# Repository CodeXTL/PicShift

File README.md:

# PicShift
## Overview
Welcome to the overview of the project (currently) known as PixShift. Inspired by the DIY Image Sensor and Digital Camera by Sean Hodgins (source), the goal of this project is to create a portable camera with a 64-pixel camera sensor that is mounted on a mechanically shifted stage so that images at a higher resolution can be obtained. The camera sensor will be created from scratch by laying out an 8 by 8 grid of light sensors (or phototransistors) on a custom PCB. Since an 8 pixels by 8 pixels image is not very interesting, we will mount the camera sensor PCB on a motorized mechanical XY stage so that we may shift the small senser over a wider area to capture multiple samples in order to stitch them into a higher resolution image. The stitching of samples will be done through software on a STM32F411RET6 microcontroller, residing on the NUCLEO-F411RE development board. The resulting image data will be saved onto a microSD card through a breakout board. For focusing the light onto the sensible region, we plan on using an existing convex lense (perhaps a magnifying lens or some kind of camera lens) 

## Objectives
-	Design and create a working PCB for an array of 8 by 8 light sensors
-	Design and create a mechanical XY stage in a small form factor.
-	Design and create a body to house all components so that the final project is portable.

## Expectation
The expectation for the project is quite simple. The final product should be able to take an image at the click of a button, store that image onto a microSD card, and when we open the image on a computer, it should resemble the scene. If it can do all that, that is an ‘A’. And the measure of even greater success would just be how much more we can make the image resemble the scene; the clear, the better. 

## Mid-Project Review Goal
By the time of the mid-project review, I aim to have the following deliverables:
-	A working camera sensor PCB
-	A prototype for the motorized XY stage

## Cost
Work-in Progress

## Resources
-	Instructables: DIY Image Sensor and Digital Camera
  -	Github: LINK
-	YouTube: Microscope Automated XY Stage: 3D Printing test
  - They salvaged a CD-ROM drive and made a highly precise XY stage for microscope slides
  - The motor from the CD-ROM drive is apparently called a sled motor, which seems like a stepper motor attached to a very long screw (might look for alternatives if it becomes hard to acquire an old CD drive)
-	st.com: User Manual for NUCLEO-F411RE
-	DigiKey: ALS-PT19-315C/L177/TR8
-	LCSC: EVERLIGHT ALS-PT19-315C/L177/TR8

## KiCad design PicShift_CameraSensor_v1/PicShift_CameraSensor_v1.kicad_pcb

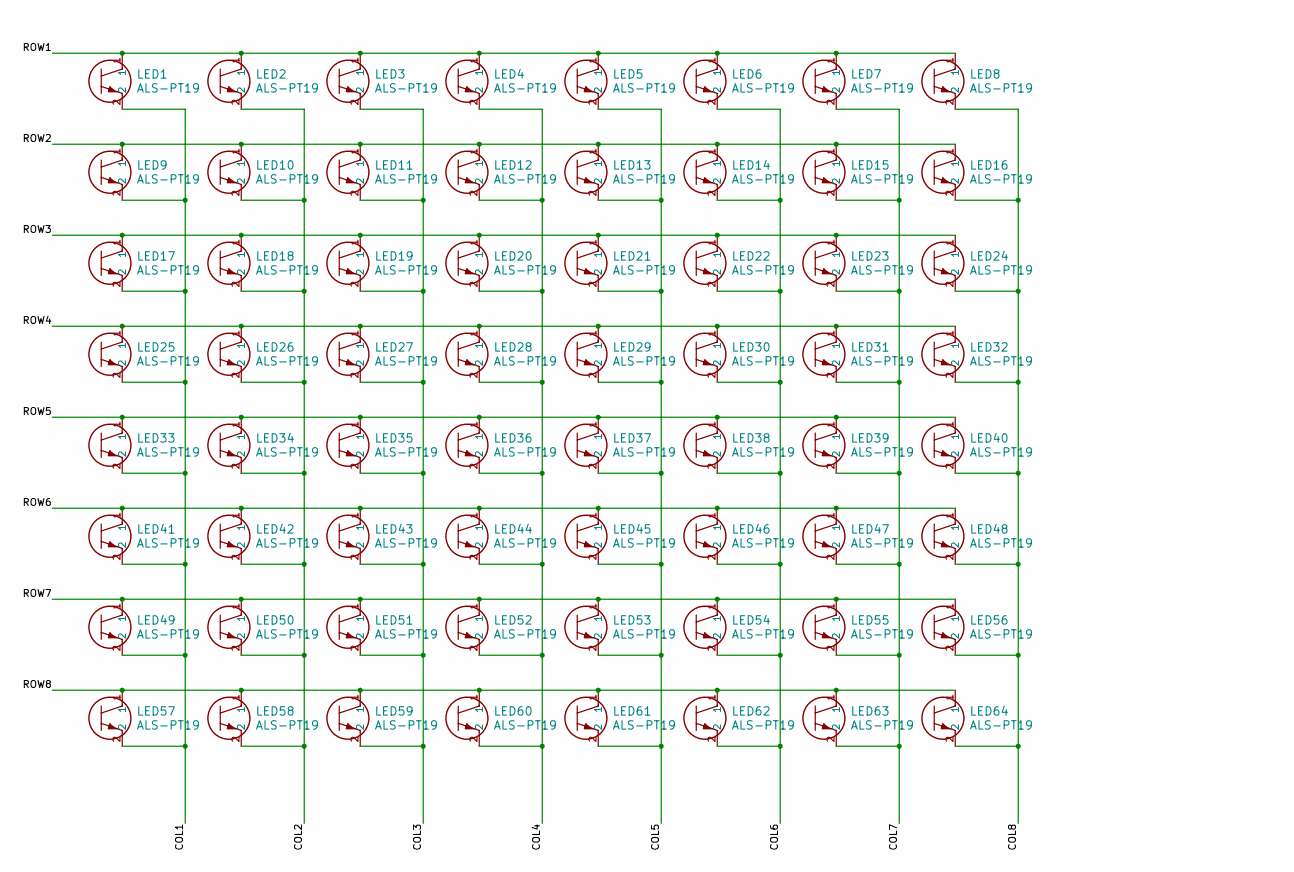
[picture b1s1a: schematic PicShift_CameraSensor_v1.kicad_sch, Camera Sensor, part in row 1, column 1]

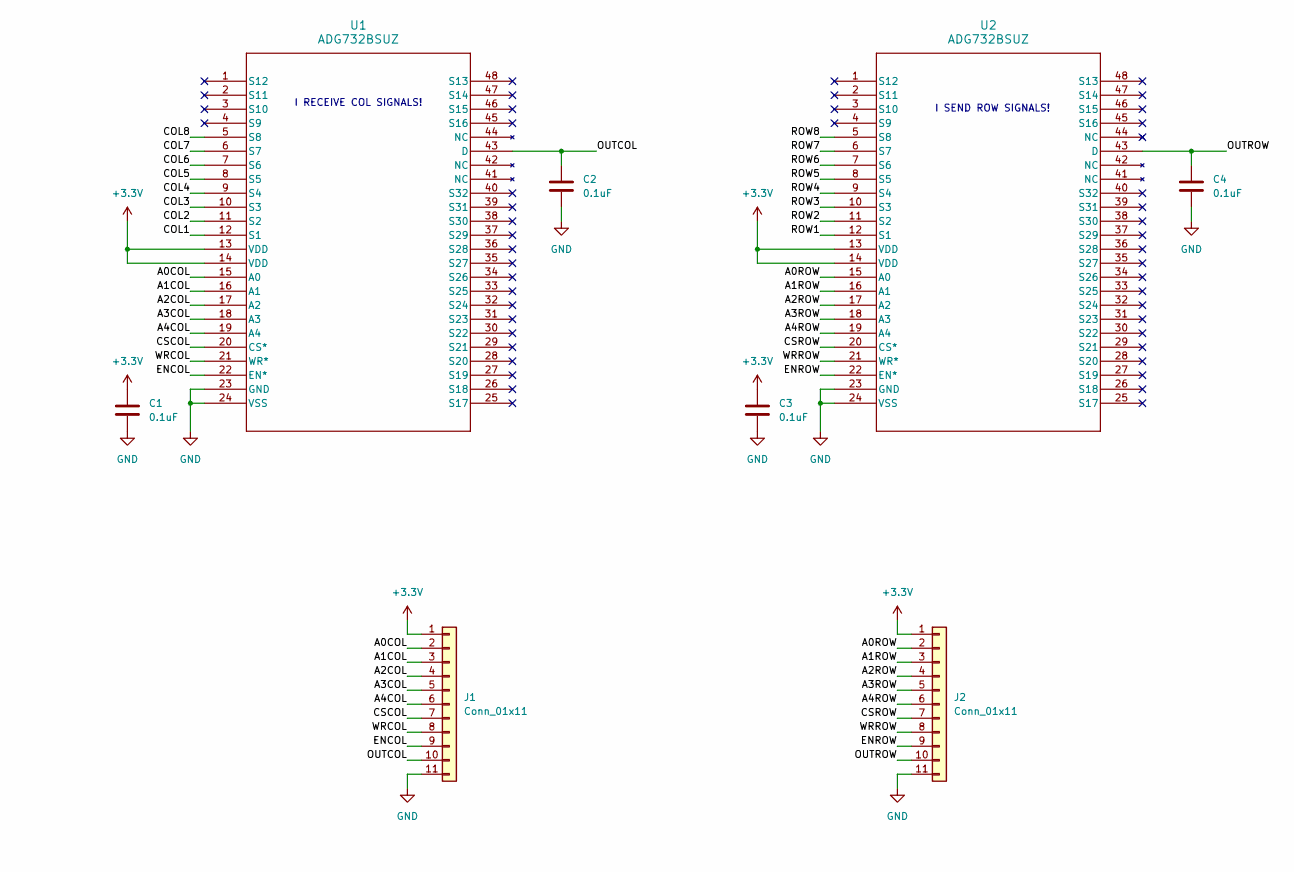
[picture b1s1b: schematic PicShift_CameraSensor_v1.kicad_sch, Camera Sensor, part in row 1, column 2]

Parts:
C1, C2, C3, C4: 0.1uF; C_0805_2012Metric_Pad1.18x1.45mm_HandSolder
J1, J2: Conn_01x11; PinHeader_1x11_P1.00mm_Vertical
LED1, LED2, LED3, LED4, LED5, LED6, LED7, LED8, LED9, LED10, LED11, LED12, LED13, LED14, LED15, LED16, LED17, LED18, LED19, LED20, LED21, LED22, LED23, LED24, LED25, LED26, LED27, LED28, LED29, LED30, LED31, LED32, LED33, LED34, LED35, LED36, LED37, LED38, LED39, LED40, LED41, LED42, LED43, LED44, LED45, LED46, LED47, LED48, LED49, LED50, LED51, LED52, LED53, LED54, LED55, LED56, LED57, LED58, LED59, LED60, LED61, LED62, LED63, LED64: ALS-PT19; LED_77&slash_TR8_EVE
U1, U2: ADG732BSUZ; SU_48_ADI

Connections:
+3.3V: C1.1, C3.1, J1.1, J2.1, U1.13 (VDD), U1.14 (VDD), U2.13 (VDD), U2.14 (VDD)
/A0COL: J1.2, U1.15 (A0)
/A0ROW: J2.2, U2.15 (A0)
/A1COL: J1.3, U1.16 (A1)
/A1ROW: J2.3, U2.16 (A1)
/A2COL: J1.4, U1.17 (A2)
/A2ROW: J2.4, U2.17 (A2)
/A3COL: J1.5, U1.18 (A3)
/A3ROW: J2.5, U2.18 (A3)
/A4COL: J1.6, U1.19 (A4)
/A4ROW: J2.6, U2.19 (A4)
/COL1: LED1.2, LED9.2, LED17.2, LED25.2, LED33.2, LED41.2, LED49.2, LED57.2, U1.12 (S1)
/COL2: LED2.2, LED10.2, LED18.2, LED26.2, LED34.2, LED42.2, LED50.2, LED58.2, U1.11 (S2)
/COL3: LED3.2, LED11.2, LED19.2, LED27.2, LED35.2, LED43.2, LED51.2, LED59.2, U1.10 (S3)
/COL4: LED4.2, LED12.2, LED20.2, LED28.2, LED36.2, LED44.2, LED52.2, LED60.2, U1.9 (S4)
/COL5: LED5.2, LED13.2, LED21.2, LED29.2, LED37.2, LED45.2, LED53.2, LED61.2, U1.8 (S5)
/COL6: LED6.2, LED14.2, LED22.2, LED30.2, LED38.2, LED46.2, LED54.2, LED62.2, U1.7 (S6)
/COL7: LED7.2, LED15.2, LED23.2, LED31.2, LED39.2, LED47.2, LED55.2, LED63.2, U1.6 (S7)
/COL8: LED8.2, LED16.2, LED24.2, LED32.2, LED40.2, LED48.2, LED56.2, LED64.2, U1.5 (S8)
/CSCOL: J1.7, U1.20 (CS*)
/CSROW: J2.7, U2.20 (CS*)
/ENCOL: J1.9, U1.22 (EN*)
/ENROW: J2.9, U2.22 (EN*)
/OUTCOL: C2.1, J1.10, U1.43 (D)
/OUTROW: C4.1, J2.10, U2.43 (D)
/ROW1: LED1.1, LED2.1, LED3.1, LED4.1, LED5.1, LED6.1, LED7.1, LED8.1, U2.12 (S1)
/ROW2: LED9.1, LED10.1, LED11.1, LED12.1, LED13.1, LED14.1, LED15.1, LED16.1, U2.11 (S2)
/ROW3: LED17.1, LED18.1, LED19.1, LED20.1, LED21.1, LED22.1, LED23.1, LED24.1, U2.10 (S3)
/ROW4: LED25.1, LED26.1, LED27.1, LED28.1, LED29.1, LED30.1, LED31.1, LED32.1, U2.9 (S4)
/ROW5: LED33.1, LED34.1, LED35.1, LED36.1, LED37.1, LED38.1, LED39.1, LED40.1, U2.8 (S5)
/ROW6: LED41.1, LED42.1, LED43.1, LED44.1, LED45.1, LED46.1, LED47.1, LED48.1, U2.7 (S6)
/ROW7: LED49.1, LED50.1, LED51.1, LED52.1, LED53.1, LED54.1, LED55.1, LED56.1, U2.6 (S7)
/ROW8: LED57.1, LED58.1, LED59.1, LED60.1, LED61.1, LED62.1, LED63.1, LED64.1, U2.5 (S8)
/WRCOL: J1.8, U1.21 (WR*)
/WRROW: J2.8, U2.21 (WR*)
GND: C1.2, C2.2, C3.2, C4.2, J1.11, J2.11, U1.23 (GND), U1.24 (VSS), U2.23 (GND), U2.24 (VSS)

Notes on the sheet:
I SEND ROW SIGNALS!
I RECEIVE COL SIGNALS!

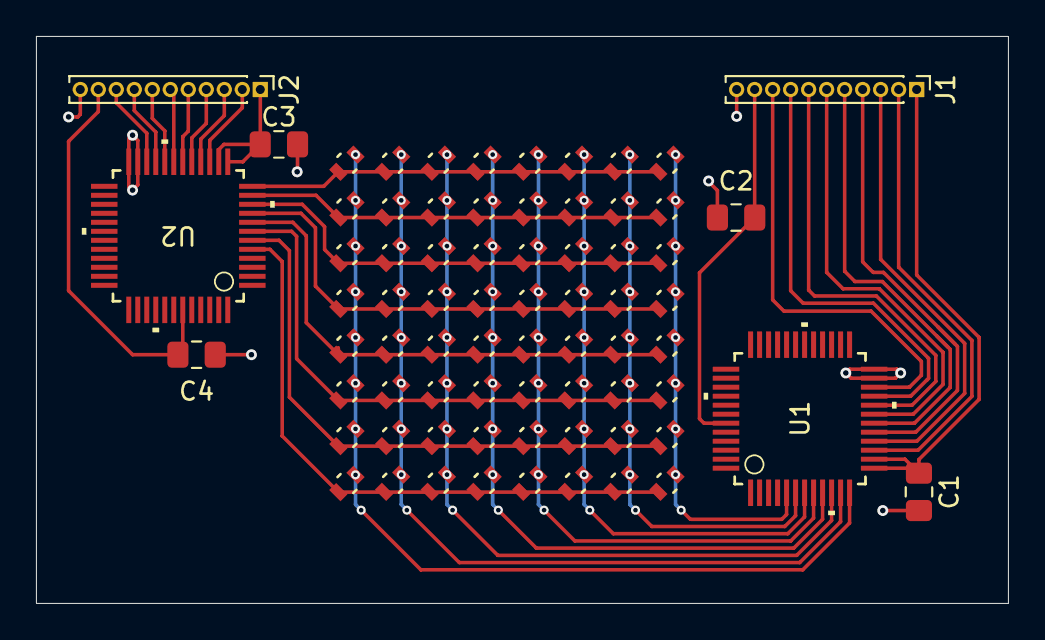
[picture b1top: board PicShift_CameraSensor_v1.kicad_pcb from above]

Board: 2 copper layers, 54.0 x 31.5 mm, 72 parts (0 on the bottom side), 36 nets.

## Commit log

2025-11-10 Added Camera sensor PCB project
2025-11-12 Added symbols and footprints, added 8x8 grid schematic
2025-11-12 Added pcb
2025-11-12 Fixed all DRC for OSHPARK
2025-11-12 Added step models for mux and phototransistors
2025-11-12 Added models to pcb
2025-11-12 updated shape of PCB
